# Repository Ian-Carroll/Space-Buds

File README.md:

# Space Buds 

Space Buds team repository for NASA's 2021 International Space Apps Challenge - "Let It Go (Without A Bang)".

Please find our pitch video [here](https://www.youtube.com/watch?v=mZa6cD9xq2c), or feel free to browse this repository for more information. This README provides an overview of the information contained within the repository.

We would also like to highlight our design report, which can be found under `Documentation/report.pdf`.

## Mechanical Design

[Please note that the gearbox casing should not be spinning in the above animation, and the spring is missing]

[Please note that the spring should be compressed in the above render]

## Electrical Design

## Documentation Files
File | Contents
---- | --------
`Documentation/report.pdf` | A complete design report detailing every aspect of our project. Includes renders, drawings and references.
`Documentation/presentation.pdf` | Our 5-slide pitch presentation, presented [here](https://www.youtube.com/watch?v=mZa6cD9xq2c).
`Documentation/Datasheets/Electrical/` | Datasheets for all off-the-shelf mechanical components used in our design.
`Documentation/Datasheets/Mechanical/` | Datasheets for all off-the-shelf electrical components used in our design.

## Mechanical Files
File | Contents
---- | --------
`Mechanical/animation.mp4` | An animation of the system deploying.
`Mechanical/Drawings/SolidWorks/` | SolidWorks mechanical drawings files.
`Mechanical/Drawings/Images/` | SolidWorks mechanical drawings as JPEG or PDF files.
`Mechanical/Models/SolidWorks/` | SolidWorks 3D model files.
`Mechanical/Renders/` | Mechanical part renders.

## Electrical Files

File | Contents
---- | --------
`Electrical/KiCad/` | KiCAD electrical CAD files for the PCB.
`Electrical/Renders/` | Renders of the PCB, generated by KiCAD.
`Electrical/layout.png` | An image of the PCB's layout.
`Electrical/schematic.png` | An image of the PCB's schematic.

## Contributors

* Noah Bailey
* Ian Carroll
* Aidan Clark
* Nick Cusack
* Madison Squires
* Shane Williams

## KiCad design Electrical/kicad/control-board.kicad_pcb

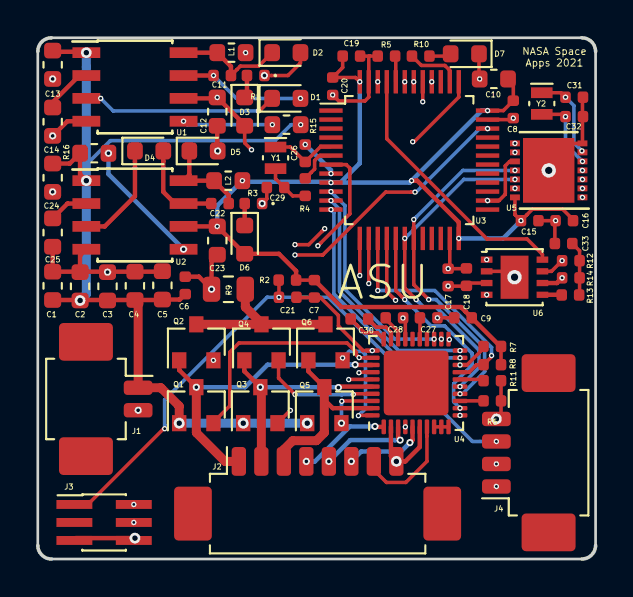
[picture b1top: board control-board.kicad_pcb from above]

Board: 4 copper layers, 31.0 x 29.0 mm, 76 parts (0 on the bottom side), 71 nets.

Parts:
C1, C2, C3, C4, C5, C10, C12, C13, C14, C23, C24, C25: 10u; C_0603_1608Metric
C6, C7, C8, C9, C11, C15, C17, C19, C21, C22, C30: 100n; C_0402_1005Metric
C16, C18, C20, C27, C28: 1u; C_0402_1005Metric
C26, C29, C31, C32: 10p; C_0402_1005Metric
C33: 4.7n; C_0402_1005Metric
D1, D4: DIODE; D_0603_1608Metric
D2, D5: D_Zener; D_0603_1608Metric
D3, D6, D7: LED; LED_0603_1608Metric
J1: Conn_01x02; Molex_PicoBlade_53261-0271_1x02-1MP_P1.25mm_Horizontal
J2: Conn_01x08; Molex_PicoBlade_53261-0871_1x08-1MP_P1.25mm_Horizontal
J3: Conn_02x03_Odd_Even; PinHeader_2x03_P1.00mm_Vertical_SMD
J4: Conn_01x04; Molex_PicoBlade_53261-0471_1x04-1MP_P1.25mm_Horizontal
L1, L2: 2.2u; L_0603_1608Metric
Q1, Q2, Q3, Q4, Q5, Q6: Q_NMOS_DGS; SOT-23
R1: 510; LED_0402_1005Metric
R2, R7, R8: 4.7k; R_0402_1005Metric
R3: 330; LED_0402_1005Metric
R4: 400; R_0402_1005Metric
R5: 1k; R_0402_1005Metric
R6, R11: 10k; R_0402_1005Metric
R9: 0.25; R_0805_2012Metric
R10: 330; R_0402_1005Metric
R12, R14: 60; R_0402_1005Metric
R13: 300; R_0402_1005Metric
R15, R16: 1k; R_0603_1608Metric
U1: NCV891130PD50R2G; SOIC-8_3.9x4.9mm_P1.27mm
U2: NCV891130PD33R2G; SOIC-8_3.9x4.9mm_P1.27mm
U3: STM32L031C6Tx; LQFP-48_7x7mm_P0.5mm
U4: DRV8308; QFN-40-1EP_5x5mm_P0.4mm_EP3.6x3.6mm
U5: MCP2517FD-xJHA; DFN-14-1EP_4x4mm_P0.5mm_EP2.86x3.6mm
U6: MCP2561-E-MF; DFN-8-1EP_3x3mm_P0.65mm_EP1.55x2.4mm
Y1: 25MHz/8pF; Crystal_SMD_MicroCrystal_CM9V-T1A-2Pin_1.6x1.0mm
Y2: 20MHz/8pF; Crystal_SMD_MicroCrystal_CM9V-T1A-2Pin_1.6x1.0mm

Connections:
+3V3: C7.1, C8.1, C9.1, C10.1, C15.1, C16.1, C19.1, C20.1, C23.2, D6.2, L2.2, R2.1, R7.1, R8.1, U2.6, U3.9, U3.24, U3.36, U3.48, U5.14
+5V: C12.2, C17.1, C18.1, D3.2, L1.2, U1.6, U6.3
+24V: C1.1, C2.1, C3.1, C4.1, C5.1, C6.1, C13.1, C24.1, C28.1, J1.1, Q1.1, Q3.1, Q5.1, R15.2, R16.2, U1.1, U2.1, U4.27
/+5V_HALL: J2.7, U4.7
/CANH: J4.1, R12.1, U6.7
/CANL: J4.2, R14.2, U6.6
/CAN_CLKO: U3.43, U5.3
/CAN_OSC_IN: C31.1, U5.6, Y2.1
/CAN_OSC_OUT: C32.1, U5.5, Y2.2
/CAN_STBY: U3.45, U6.8
/DRV_BRK: U3.11, U4.20
/DRV_DIR: U3.13, U4.21
/DRV_EN: U3.14, U4.22
/DRV_FREQ: U3.12, U4.19
/DRV_RST: U3.10, U4.23
/MCU_OSC_IN: C26.1, U3.5, Y1.1
/MCU_OSC_OUT: R4.1, U3.6
/MISO: U3.18, U4.15, U5.12
/MOSI: U3.19, U4.14, U5.11
/RX_CAN: U5.2, U6.4
/SCLK: U3.26, U4.11, U5.10
/SWCLK: J3.2, U3.37
/SWDIO: J3.4, U3.34
/TX_CAN: U5.1, U6.1
/U_HALL: J2.4, U4.1
/U_PHA: J2.1, Q1.3, Q2.1, U4.33
/V_HALL: J2.5, U4.3
/V_PHA: J2.2, Q3.3, Q4.1, U4.36
/W_HALL: J2.6, U4.5
/W_PHA: J2.3, Q5.3, Q6.1, U4.39
/~CAN_CS: U3.46, U5.13
/~CAN_INT: U3.40, U5.4
/~CAN_INT_RX: U3.41, U5.9
/~CAN_INT_TX: U3.42, U5.8
/~DRV_CS: U3.17, U4.12
/~DRV_FLT: R8.2, U3.15, U4.17
/~DRV_LCK: R7.2, U3.16, U4.18
/~MCU_RST: C21.1, J3.1, J4.3, R2.2, U3.7
GND: C1.2, C2.2, C3.2, C4.2, C5.2, C6.2, C7.2, C8.2, C9.2, C10.2, C12.1, C13.2, C14.2, C15.2, C16.2, C17.2, C18.2, C19.2, C20.2, C21.2, C23.1, C24.2, C25.2, C26.2, C27.2, C29.2, C31.2, C32.2, C33.1, D2.2, D5.2, D7.1, J1.2, J2.8, J3.5, J3.6, J4.4, R1.1, R3.1, R5.2, R6.1, R9.2, R11.2, U1.4, U2.4, U3.8, U3.23, U3.35, U3.47, U4.2, U4.4, U4.6, U4.31, U5.7, U5.15, U6.2, U6.9
unnamed: C11.1, D2.1, L1.1, U1.8
unnamed: C11.2, D1.2, U1.7
unnamed: C14.1, U1.2
unnamed: C22.1, D5.1, L2.1, U2.8
unnamed: C22.2, D4.2, U2.7
unnamed: C25.1, U2.2
unnamed: C27.1, U4.25
unnamed: C28.2, U4.28
unnamed: C29.1, R4.2, Y1.2
unnamed: C30.1, U4.30
unnamed: C30.2, U4.29
unnamed: C33.2, R12.2, R13.1, R14.1
unnamed: D1.1, U1.3
unnamed: D3.1, R1.2
unnamed: D4.1, U2.3
unnamed: D6.1, R3.2
unnamed: D7.2, R10.1
unnamed: Q1.2, U4.32
unnamed: Q2.2, U4.34
unnamed: Q2.3, Q4.3, Q6.3, R9.1
unnamed: Q3.2, U4.35
unnamed: Q4.2, U4.37
unnamed: Q5.2, U4.38
unnamed: Q6.2, U4.40
unnamed: R5.1, U3.44
unnamed: R6.2, U4.13
unnamed: R10.2, U3.38
unnamed: R11.1, U4.16
unnamed: R13.2, U6.5
unnamed: R15.1, U1.5
unnamed: R16.1, U2.5
unnamed: U4.8, U4.9, U4.10

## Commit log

2021-10-03 Initial Repo Structure.
2021-10-03 Added Datasheets subfolder.
2021-10-03 Add electrical datasheets.
2021-10-03 Add PCB CAD files.
2021-10-03 Add PCB layout and schematic.
2021-10-03 Add PCB renders.
2021-10-03 Add mechanical datasheets.
2021-10-03 Initial commit of README.
2021-10-04 Add renders and models to README.md.
2021-10-04 Rename electrical directories.
2021-10-04 Add mechanical drawings.
2021-10-04 Add mechanical models.
2021-10-04 Add mechanical renders.
2021-10-04 Add mechanical animation.
2021-10-04 Add final report.
2021-10-04 Rename report.
2021-10-04 Add presentation PDF.
2021-10-04 Rename SolidWorks directories.
2021-10-04 Add file paths to README.md.
2021-10-04 Update README.md.
